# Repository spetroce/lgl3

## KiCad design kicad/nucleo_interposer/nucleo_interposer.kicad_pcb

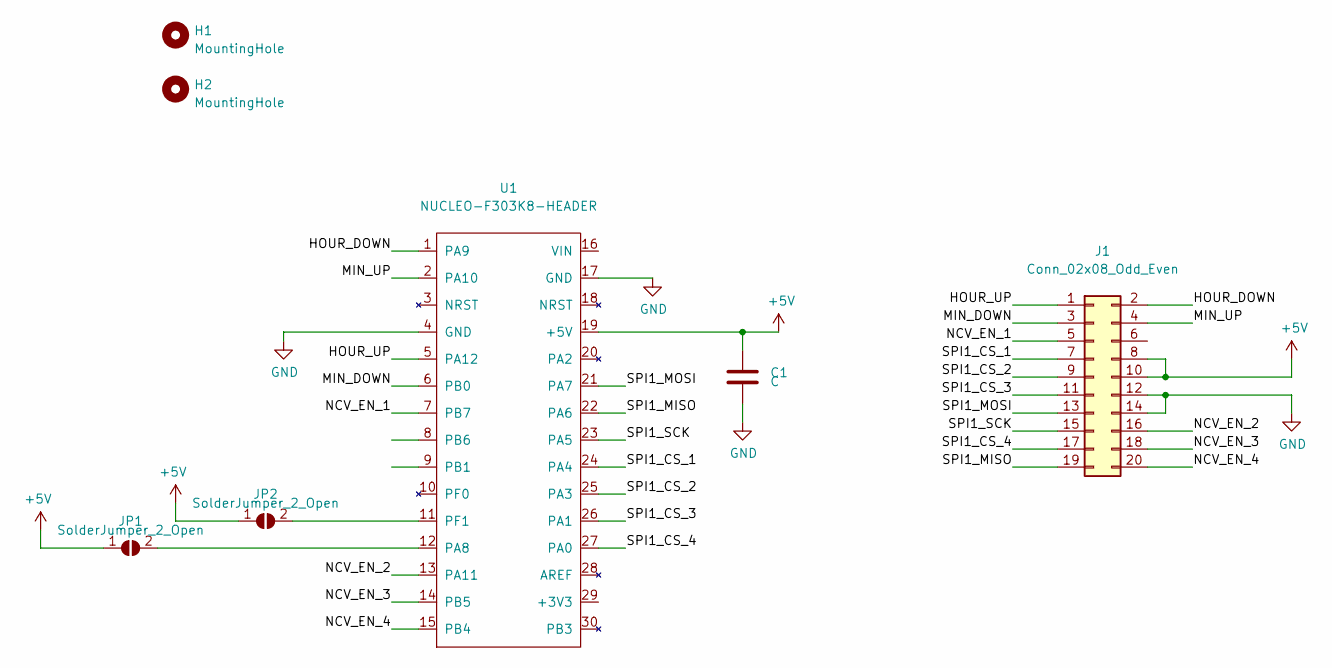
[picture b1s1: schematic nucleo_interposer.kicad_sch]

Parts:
C1: C; C_1206_3216Metric
H1, H2: MountingHole; MountingHole_3.2mm_M3
J1: Conn_02x08_Odd_Even; PinHeader_2x10_P2.54mm_Vertical
JP1, JP2: SolderJumper_2_Open; SolderJumper-2_P1.3mm_Open_TrianglePad1.0x1.5mm
U1: NUCLEO-F303K8-HEADER

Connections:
+5V: C1.2, J1.8, J1.10, JP1.1 (A), JP2.1 (A), U1.19 (+5V)
/HOUR_DOWN: J1.2, U1.1 (PA9)
/HOUR_UP: J1.1, U1.5 (PA12)
/MIN_DOWN: J1.3, U1.6 (PB0)
/MIN_UP: J1.4, U1.2 (PA10)
/NCV_EN_1: J1.5, U1.7 (PB7)
/NCV_EN_2: J1.16, U1.13 (PA11)
/NCV_EN_3: J1.18, U1.14 (PB5)
/NCV_EN_4: J1.20, U1.15 (PB4)
/SPI1_CS_1: J1.7, U1.24 (PA4)
/SPI1_CS_2: J1.9, U1.25 (PA3)
/SPI1_CS_3: J1.11, U1.26 (PA1)
/SPI1_CS_4: J1.17, U1.27 (PA0)
/SPI1_MISO: J1.19, U1.22 (PA6)
/SPI1_MOSI: J1.13, U1.21 (PA7)
/SPI1_SCK: J1.15, U1.23 (PA5)
GND: C1.1, J1.12, J1.14, U1.4 (GND), U1.17 (GND)
unnamed: JP1.2 (B), U1.12 (PA8)
unnamed: JP2.2 (B), U1.11 (PF1)

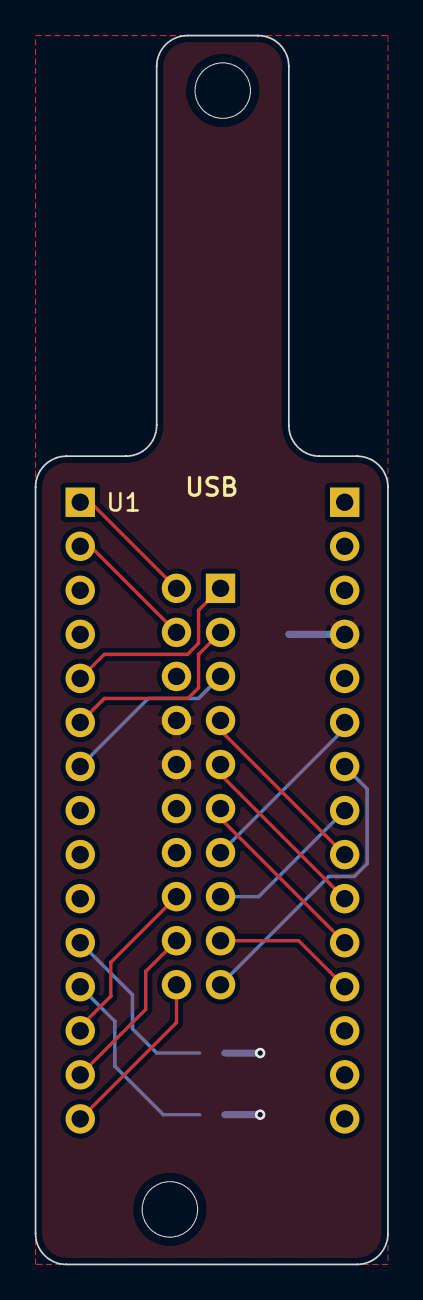
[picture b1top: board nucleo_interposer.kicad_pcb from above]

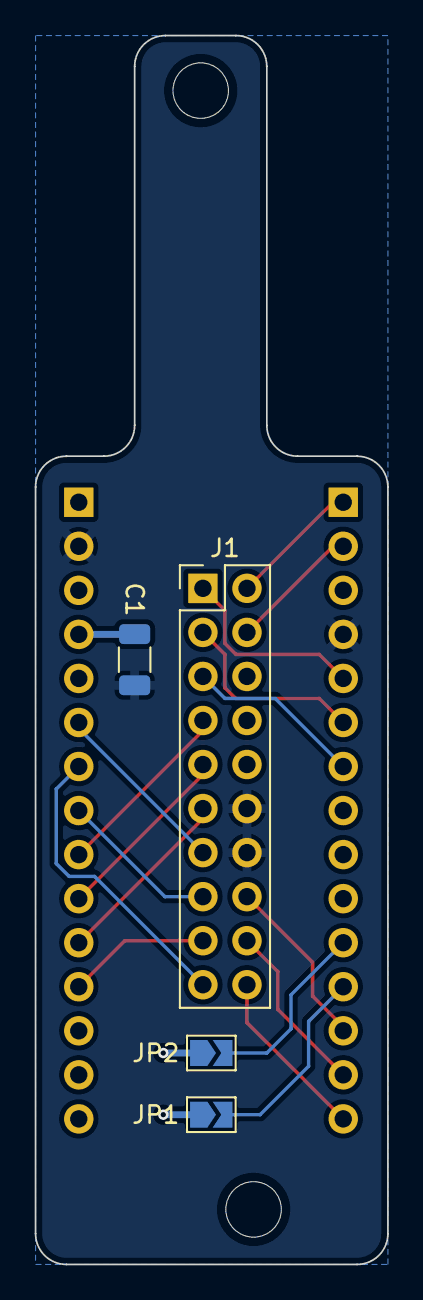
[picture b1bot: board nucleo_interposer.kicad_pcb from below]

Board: 2 copper layers, 20.3 x 70.9 mm, 7 parts (4 on the bottom side), 19 nets.

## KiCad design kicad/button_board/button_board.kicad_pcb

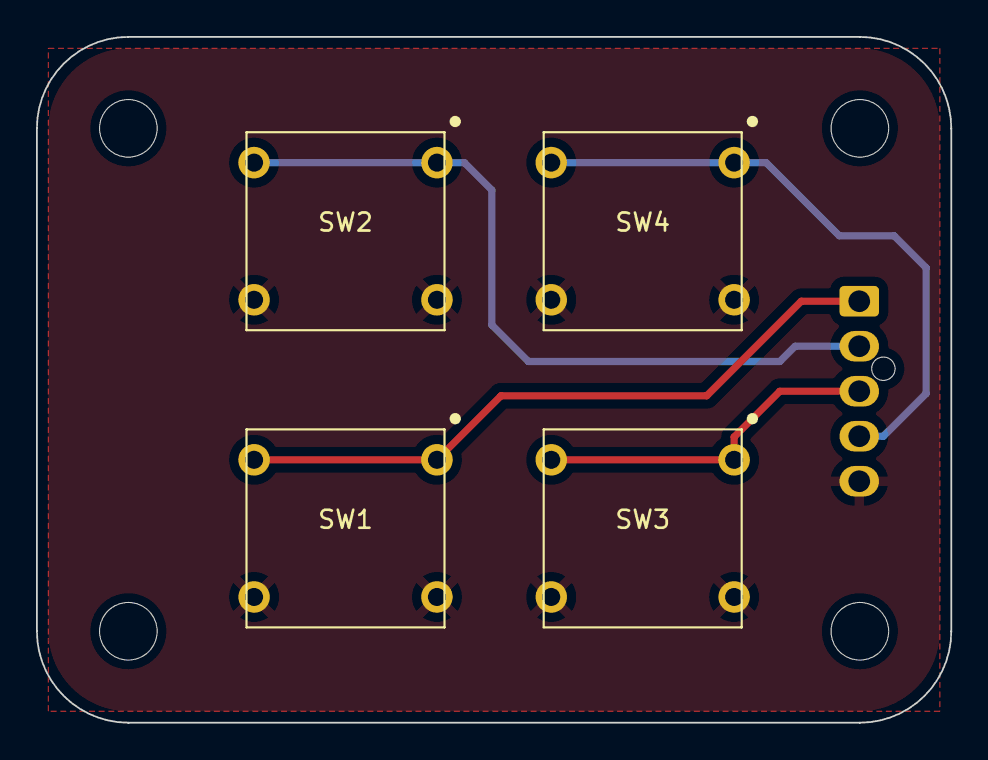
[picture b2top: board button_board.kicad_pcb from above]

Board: 2 copper layers, 50.8 x 38.1 mm, 9 parts (1 on the bottom side), 5 nets.

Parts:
H1, H2, H3, H4: MountingHole; MountingHole_3.2mm_M3
J1: Conn_01x05_Male; Molex_Nano-Fit_105309-xx05_1x05_P2.50mm_Vertical
SW1, SW2, SW3, SW4: apem-3eth9-15.0; 3ETH9-15.0

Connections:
/HOUR_DOWN: J1.1, SW1.1, SW1.2
/HOUR_UP: J1.2, SW2.1, SW2.2
/MIN_DOWN: J1.3, SW3.1, SW3.2
/MIN_UP: J1.4, SW4.1, SW4.2
GND: J1.5, SW1.3, SW1.4, SW2.3, SW2.4, SW3.3, SW3.4, SW4.3, SW4.4

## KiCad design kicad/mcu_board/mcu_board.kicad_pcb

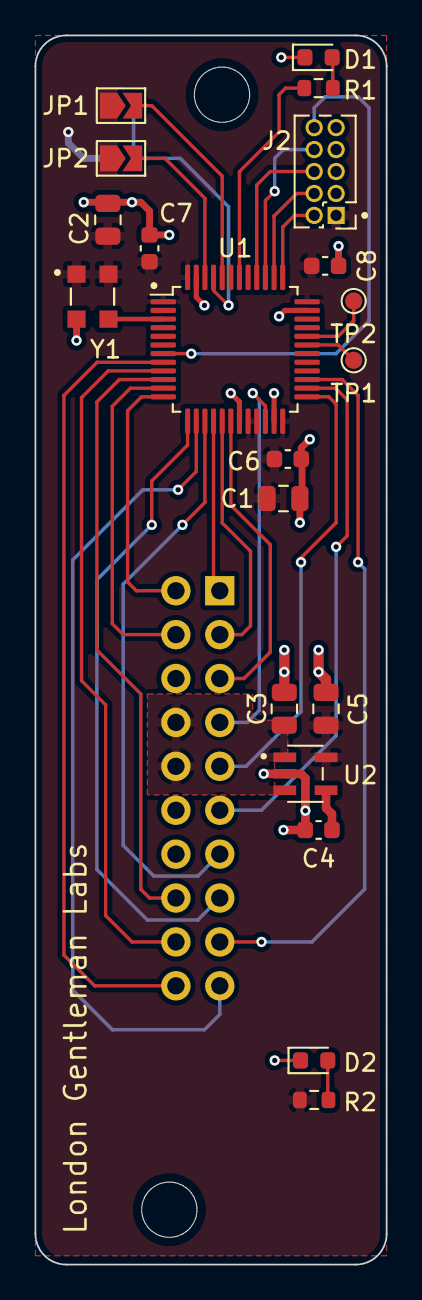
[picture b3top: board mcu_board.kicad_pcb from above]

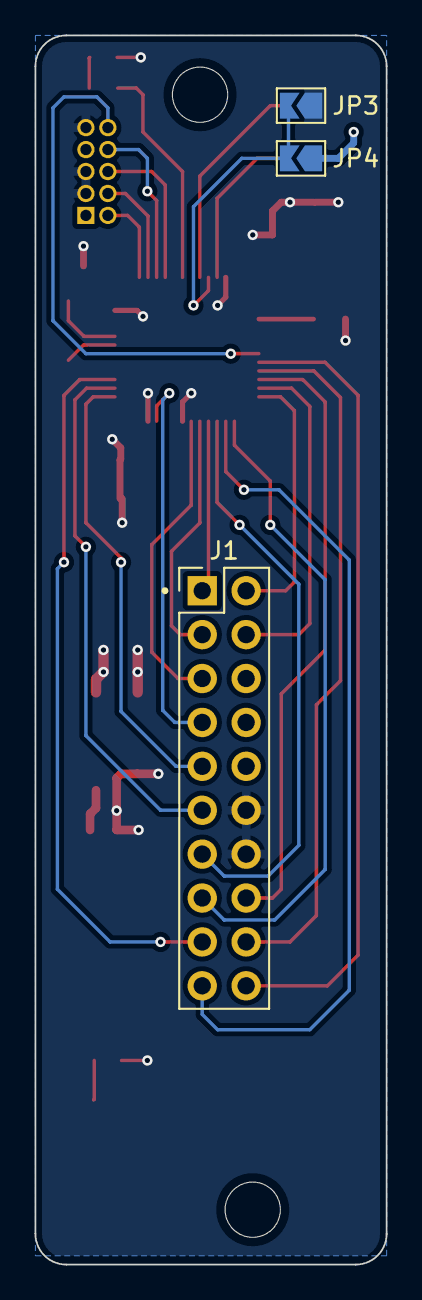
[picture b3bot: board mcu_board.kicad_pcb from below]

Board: 2 copper layers, 20.3 x 71.1 mm, 25 parts (3 on the bottom side), 33 nets.

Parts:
C1, C5: 10uF; C_0805_2012Metric
C2, C3: 1uF; C_0805_2012Metric
C4: 10nF; C_0603_1608Metric
C6, C7, C8: 100nF; C_0603_1608Metric
D1, D2: LED; LED_0603_1608Metric
H1, H2: MountingHole; MountingHole_3.2mm_M3
J1: Conn_02x08_Odd_Even; PinHeader_2x10_P2.54mm_Vertical
J2: Conn_02x05_Odd_Even; PinHeader_2x05_P1.27mm_Vertical
JP1, JP2, JP3, JP4: SolderJumper_2_Open; SolderJumper-2_P1.3mm_Open_TrianglePad1.0x1.5mm
R1, R2: 200; R_0603_1608Metric
TP1, TP2: TestPoint; TestPoint_Pad_D1.0mm
U1: STM32G431CBTx; LQFP-48_7x7mm_P0.5mm
U2: LD2985BM33R; SOT23-5L_STM
Y1: ECS-327TXO-33-TR

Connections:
+3V3: C1.1, C2.2, C5.2, C6.1, C7.2, C8.1, J2.1, JP1.1 (A), JP2.1 (A), JP4.1 (A), R2.1, U1.1 (VBAT), U1.20 (VREF+), U1.21 (VDDA), U1.24 (VDD), U1.36 (VDD), U1.48 (VDD), U2.5 (OUT), Y1.1 (OE), Y1.4 (SUPPLY_VOLTAGE)
+5V: C3.2, J1.8, J1.10, U2.1 (IN), U2.3 (INHIBIT)
/BOOT0: JP3.2 (B), JP4.2 (B), U1.45 (PB8-BOOT0)
/HOUR_DOWN: J1.2, U1.12 (PA4)
/HOUR_UP: J1.1, U1.16 (PB0)
/HW_REV_1: JP1.2 (B), U1.44 (PB7)
/HW_REV_2: JP2.2 (B), U1.46 (PB9)
/LED_GREEN: R1.1, U1.42 (PB5)
/MIN_DOWN: J1.3, U1.17 (PB1)
/MIN_UP: J1.4, U1.11 (PA3)
/NCV_EN_1: J1.5, U1.18 (PB2)
/NCV_EN_2: J1.16, U1.10 (PA2)
/NCV_EN_3: J1.18, U1.9 (PA1)
/NCV_EN_4: J1.20, U1.8 (PA0)
/NRST: J2.10, U1.7 (PG10-NRST)
/RCC_OSC32_IN: U1.3 (PC14-OSC32_IN), Y1.3 (OUTPUT)
/SPI1_CS_1: J1.7, U1.22 (PB10)
/SPI1_CS_2: J1.9, U1.25 (PB11)
/SPI1_CS_3: J1.11, U1.26 (PB12)
/SPI1_CS_4: J1.17, U1.27 (PB13)
/SPI1_MISO: J1.19, U1.14 (PA6)
/SPI1_MOSI: J1.13, U1.15 (PA7)
/SPI1_SCK: J1.15, U1.13 (PA5)
/SYS_JTCK-SWCLK: J2.4, U1.38 (PA14)
/SYS_JTDI: J2.8, U1.39 (PA15)
/SYS_JTDO-SWO: J2.6, U1.40 (PB3)
/SYS_JTMS-SWDIO: J2.2, U1.37 (PA13)
GND: C1.2, C2.1, C3.1, C4.1, C5.1, C6.2, C7.1, C8.2, D1.1 (K), D2.1 (K), J1.12, J1.14, J2.3, J2.5, J2.9, JP3.1 (A), U1.19 (VSSA), U1.23 (VSS), U1.35 (VSS), U1.47 (VSS), U2.2 (GND), Y1.2 (GND)
unnamed: D1.2 (A), R1.2
unnamed: D2.2 (A), R2.2
unnamed: TP1.1, U1.31 (PA9)
unnamed: TP2.1, U1.32 (PA10)
unnamed: C4.2, U2.4 (BYPASS)

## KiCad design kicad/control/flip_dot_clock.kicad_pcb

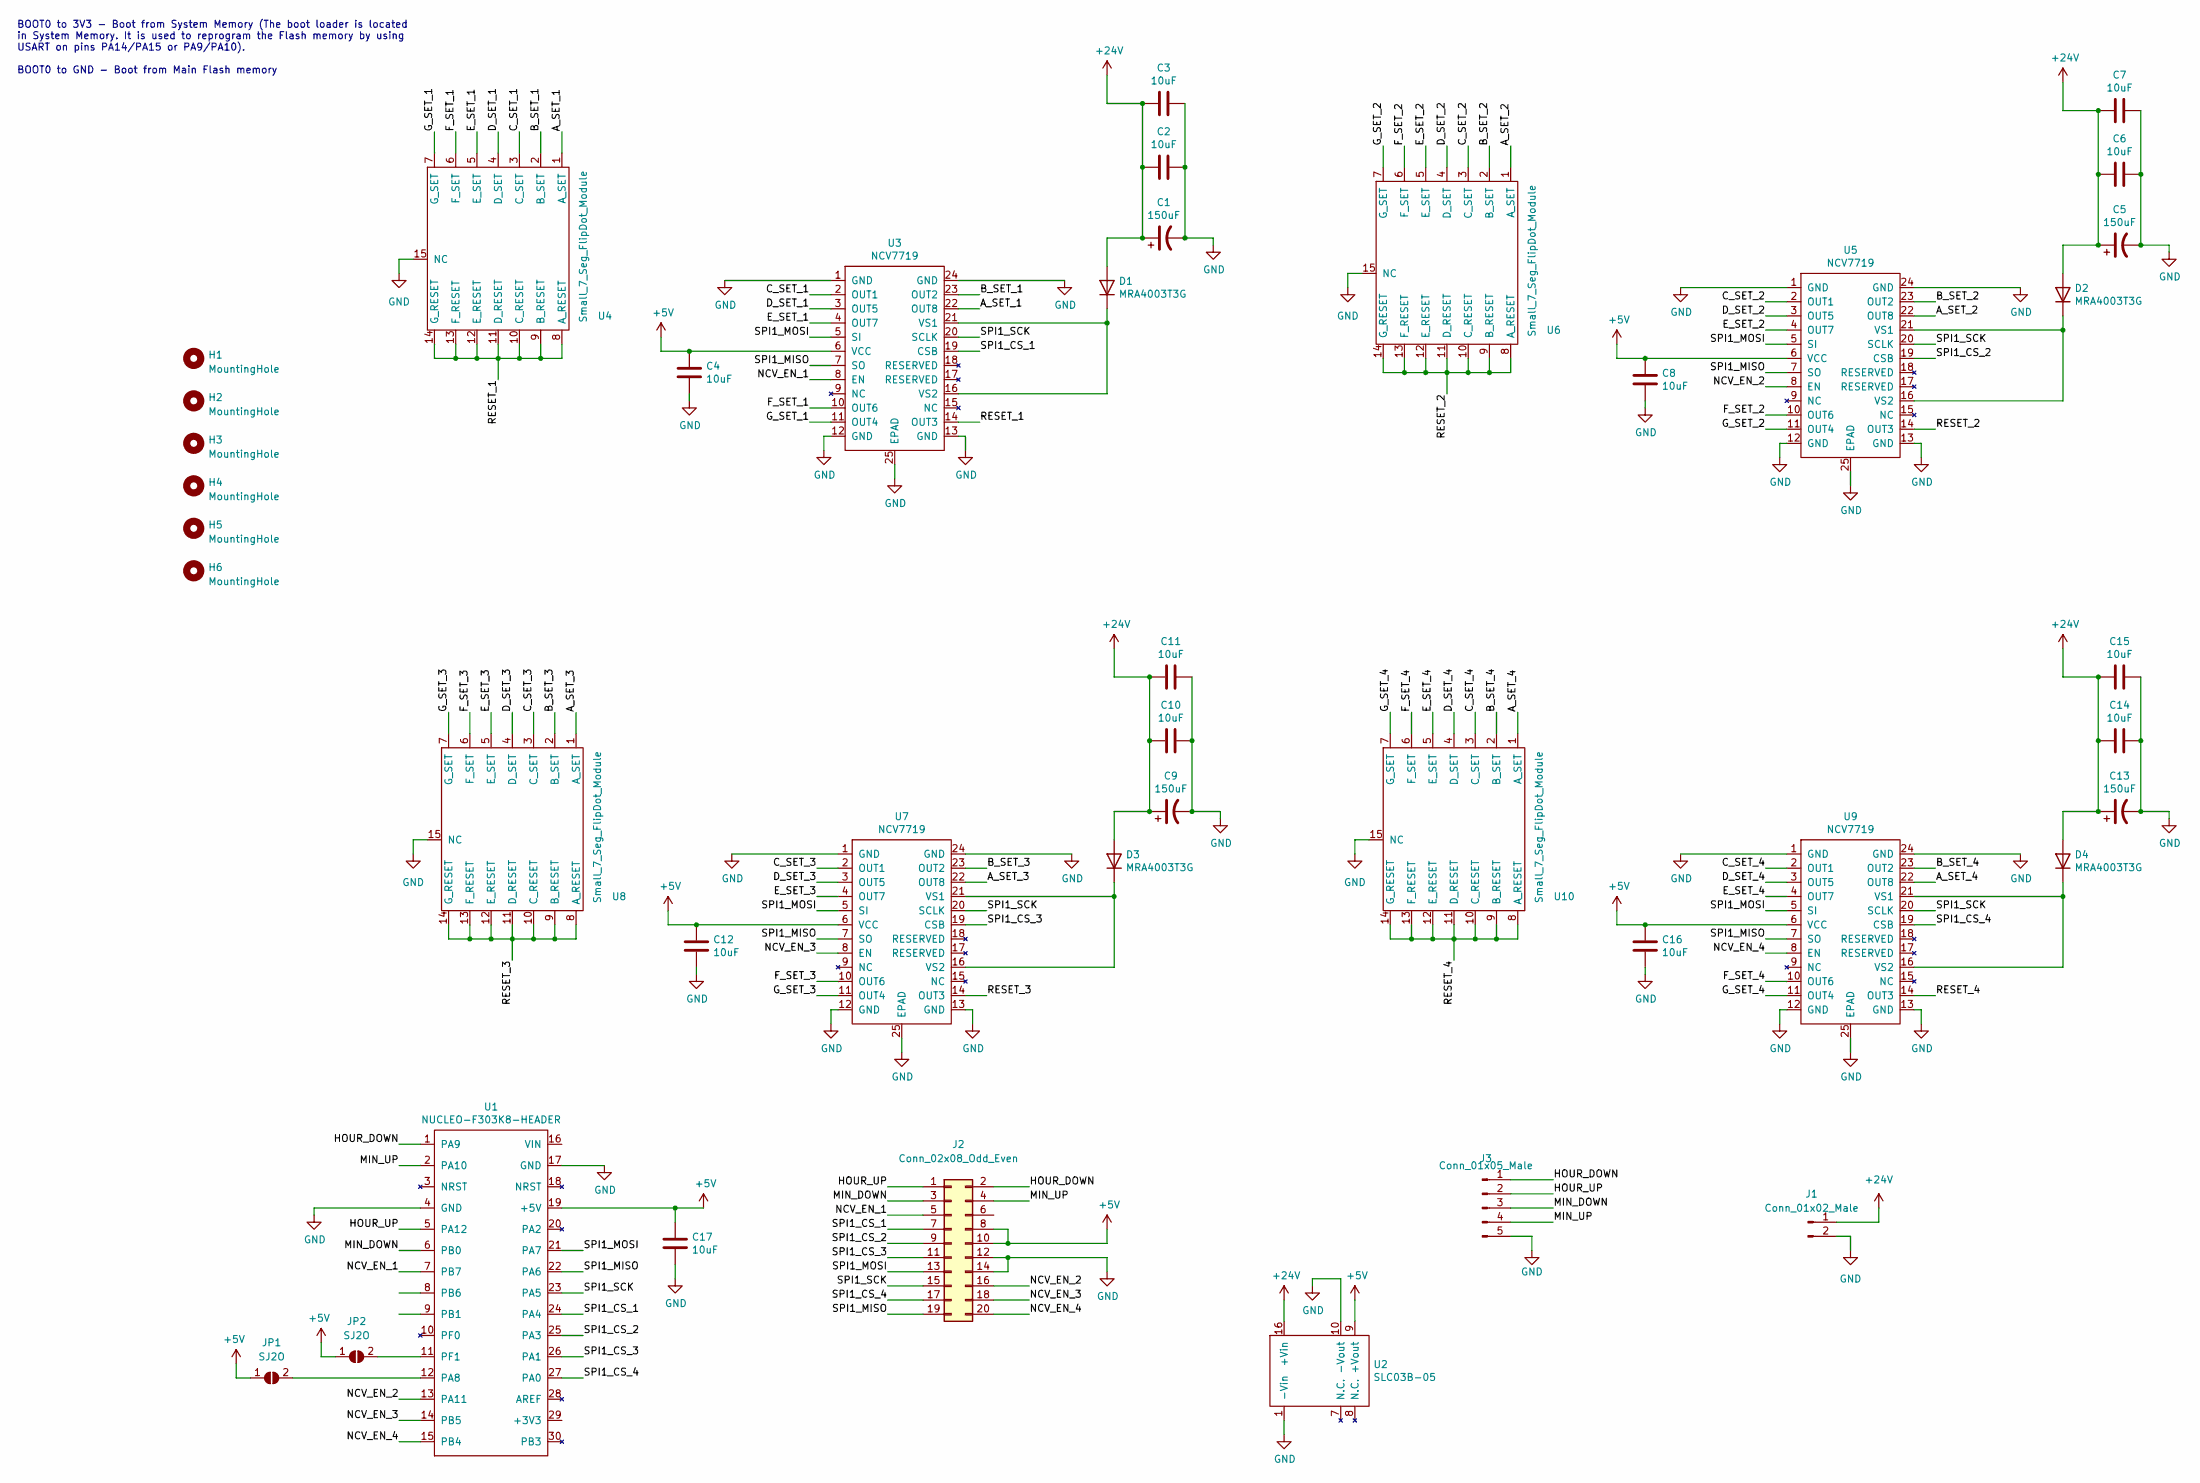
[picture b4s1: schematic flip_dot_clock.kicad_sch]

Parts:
C1, C5, C9, C13: 150uF; CP_Radial_D10.0mm_P5.00mm
C2, C3, C4, C6, C7, C8, C10, C11, C12, C14, C15, C16, C17: 10uF; C_1206_3216Metric
D1, D2, D3, D4: MRA4003T3G; D_SMA
H1, H2, H3, H4, H5, H6: MountingHole; MountingHole_3.2mm_M3
J1: Conn_01x02_Male; Molex_Micro-Fit_3.0_43650-0215_1x02_P3.00mm_Vertical
J2: Conn_02x08_Odd_Even; PinSocket_2x10_P2.54mm_Vertical
J3: Conn_01x05_Male; Molex_Nano-Fit_105309-xx05_1x05_P2.50mm_Vertical
JP1, JP2: SJ2O; SolderJumper-2_P1.3mm_Open_TrianglePad1.0x1.5mm
U1: NUCLEO-F303K8-HEADER
U2: SLC03B-05
U3, U5, U7, U9: NCV7719; SSOP-24_6.4x7.55mm_P0.65mm
U4, U6, U8, U10: Small_7_Seg_FlipDot_Module

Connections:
+5V: C4.1, C8.1, C12.1, C16.1, C17.1, J2.8, J2.10, JP1.1 (A), JP2.1 (A), U1.19 (+5V), U2.9 (+Vout), U3.6 (VCC), U5.6 (VCC), U7.6 (VCC), U9.6 (VCC)
+24V: C1.1, C2.2, C3.2, C5.1, C6.2, C7.2, C9.1, C10.2, C11.2, C13.1, C14.2, C15.2, D1.2 (A), D2.2 (A), D3.2 (A), D4.2 (A), J1.1, U2.16 (+Vin)
/A_SET_1: U3.22 (OUT8), U4.1 (A_SET)
/A_SET_2: U5.22 (OUT8), U6.1 (A_SET)
/A_SET_3: U7.22 (OUT8), U8.1 (A_SET)
/A_SET_4: U9.22 (OUT8), U10.1 (A_SET)
/B_SET_1: U3.23 (OUT2), U4.2 (B_SET)
/B_SET_2: U5.23 (OUT2), U6.2 (B_SET)
/B_SET_3: U7.23 (OUT2), U8.2 (B_SET)
/B_SET_4: U9.23 (OUT2), U10.2 (B_SET)
/C_SET_1: U3.2 (OUT1), U4.3 (C_SET)
/C_SET_2: U5.2 (OUT1), U6.3 (C_SET)
/C_SET_3: U7.2 (OUT1), U8.3 (C_SET)
/C_SET_4: U9.2 (OUT1), U10.3 (C_SET)
/D_SET_1: U3.3 (OUT5), U4.4 (D_SET)
/D_SET_2: U5.3 (OUT5), U6.4 (D_SET)
/D_SET_3: U7.3 (OUT5), U8.4 (D_SET)
/D_SET_4: U9.3 (OUT5), U10.4 (D_SET)
/E_SET_1: U3.4 (OUT7), U4.5 (E_SET)
/E_SET_2: U5.4 (OUT7), U6.5 (E_SET)
/E_SET_3: U7.4 (OUT7), U8.5 (E_SET)
/E_SET_4: U9.4 (OUT7), U10.5 (E_SET)
/F_SET_1: U3.10 (OUT6), U4.6 (F_SET)
/F_SET_2: U5.10 (OUT6), U6.6 (F_SET)
/F_SET_3: U7.10 (OUT6), U8.6 (F_SET)
/F_SET_4: U9.10 (OUT6), U10.6 (F_SET)
/G_SET_1: U3.11 (OUT4), U4.7 (G_SET)
/G_SET_2: U5.11 (OUT4), U6.7 (G_SET)
/G_SET_3: U7.11 (OUT4), U8.7 (G_SET)
/G_SET_4: U9.11 (OUT4), U10.7 (G_SET)
/HOUR_DOWN: J2.2, J3.1, U1.1 (PA9)
/HOUR_UP: J2.1, J3.2, U1.5 (PA12)
/MIN_DOWN: J2.3, J3.3, U1.6 (PB0)
/MIN_UP: J2.4, J3.4, U1.2 (PA10)
/NCV_EN_1: J2.5, U1.7 (PB7), U3.8 (EN)
/NCV_EN_2: J2.16, U1.13 (PA11), U5.8 (EN)
/NCV_EN_3: J2.18, U1.14 (PB5), U7.8 (EN)
/NCV_EN_4: J2.20, U1.15 (PB4), U9.8 (EN)
/RESET_1: U3.14 (OUT3), U4.8 (A_RESET), U4.9 (B_RESET), U4.10 (C_RESET), U4.11 (D_RESET), U4.12 (E_RESET), U4.13 (F_RESET), U4.14 (G_RESET)
/RESET_2: U5.14 (OUT3), U6.8 (A_RESET), U6.9 (B_RESET), U6.10 (C_RESET), U6.11 (D_RESET), U6.12 (E_RESET), U6.13 (F_RESET), U6.14 (G_RESET)
/RESET_3: U7.14 (OUT3), U8.8 (A_RESET), U8.9 (B_RESET), U8.10 (C_RESET), U8.11 (D_RESET), U8.12 (E_RESET), U8.13 (F_RESET), U8.14 (G_RESET)
/RESET_4: U9.14 (OUT3), U10.8 (A_RESET), U10.9 (B_RESET), U10.10 (C_RESET), U10.11 (D_RESET), U10.12 (E_RESET), U10.13 (F_RESET), U10.14 (G_RESET)
/SPI1_CS_1: J2.7, U1.24 (PA4), U3.19 (CSB)
/SPI1_CS_2: J2.9, U1.25 (PA3), U5.19 (CSB)
/SPI1_CS_3: J2.11, U1.26 (PA1), U7.19 (CSB)
/SPI1_CS_4: J2.17, U1.27 (PA0), U9.19 (CSB)
/SPI1_MISO: J2.19, U1.22 (PA6), U3.7 (SO), U5.7 (SO), U7.7 (SO), U9.7 (SO)
/SPI1_MOSI: J2.13, U1.21 (PA7), U3.5 (SI), U5.5 (SI), U7.5 (SI), U9.5 (SI)
/SPI1_SCK: J2.15, U1.23 (PA5), U3.20 (SCLK), U5.20 (SCLK), U7.20 (SCLK), U9.20 (SCLK)
GND: C1.2, C2.1, C3.1, C4.2, C5.2, C6.1, C7.1, C8.2, C9.2, C10.1, C11.1, C12.2, C13.2, C14.1, C15.1, C16.2, C17.2, J1.2, J2.12, J2.14, J3.5, U1.4 (GND), U1.17 (GND), U2.1 (-Vin), U2.10 (-Vout), U3.1 (GND), U3.12 (GND), U3.13 (GND), U3.24 (GND), U3.25 (EPAD), U4.15 (NC), U5.1 (GND), U5.12 (GND), U5.13 (GND), U5.24 (GND), U5.25 (EPAD), U6.15 (NC), U7.1 (GND), U7.12 (GND), U7.13 (GND), U7.24 (GND), U7.25 (EPAD), U8.15 (NC), U9.1 (GND), U9.12 (GND), U9.13 (GND), U9.24 (GND), U9.25 (EPAD), U10.15 (NC)
unnamed: D1.1 (K), U3.16 (VS2), U3.21 (VS1)
unnamed: D2.1 (K), U5.16 (VS2), U5.21 (VS1)
unnamed: D3.1 (K), U7.16 (VS2), U7.21 (VS1)
unnamed: D4.1 (K), U9.16 (VS2), U9.21 (VS1)
unnamed: JP1.2 (B), U1.12 (PA8)
unnamed: JP2.2 (B), U1.11 (PF1)

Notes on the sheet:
BOOT0 to 3V3 - Boot from System Memory (The boot loader is located in System Memory. It is used to reprogram the Flash memory by using USART on pins PA14/PA15 or PA9/PA10). BOOT0 to GND - Boot from Main Flash memory

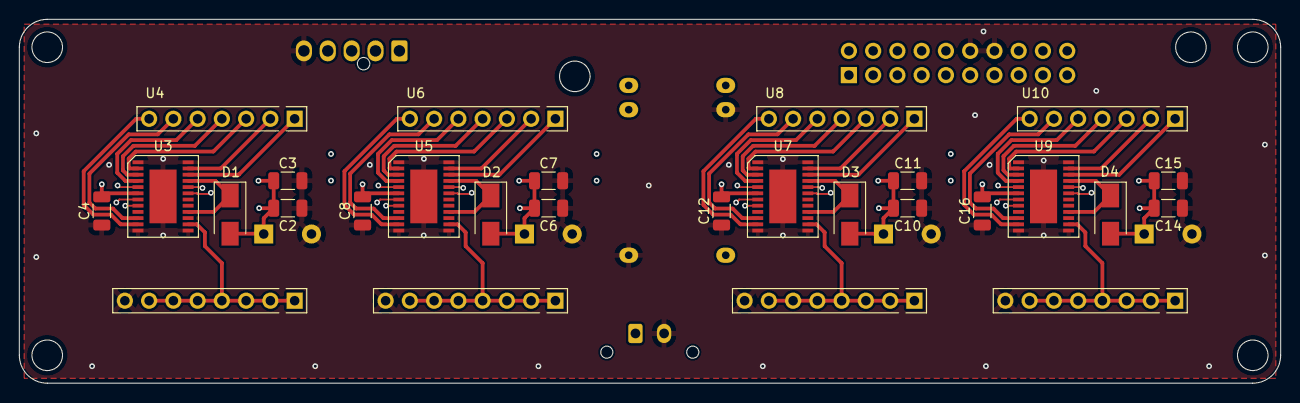
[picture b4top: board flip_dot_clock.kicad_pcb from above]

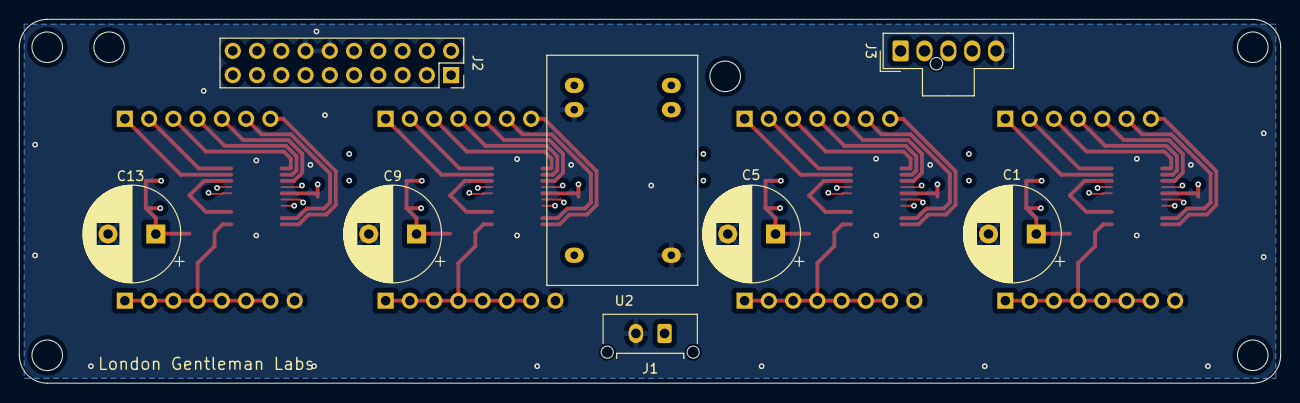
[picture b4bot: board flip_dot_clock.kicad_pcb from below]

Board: 4 copper layers, 132.1 x 38.1 mm, 38 parts (10 on the bottom side), 54 nets.

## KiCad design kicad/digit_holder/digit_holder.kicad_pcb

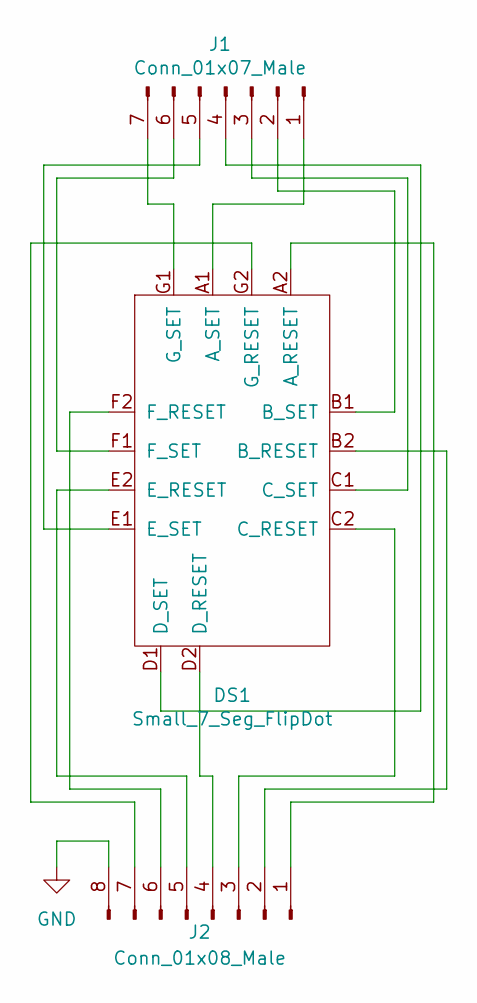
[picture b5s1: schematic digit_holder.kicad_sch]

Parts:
DS1: Small_7_Seg_FlipDot
J1: Conn_01x07_Male; PinHeader_1x07_P2.54mm_Vertical
J2: Conn_01x08_Male; PinHeader_1x08_P2.54mm_Vertical

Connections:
GND: J2.8
unnamed: DS1.A2 (A_RESET), J2.1
unnamed: DS1.A1 (A_SET), J1.1
unnamed: DS1.B2 (B_RESET), J2.2
unnamed: DS1.B1 (B_SET), J1.2
unnamed: DS1.C2 (C_RESET), J2.3
unnamed: DS1.C1 (C_SET), J1.3
unnamed: DS1.D2 (D_RESET), J2.4
unnamed: DS1.D1 (D_SET), J1.4
unnamed: DS1.E2 (E_RESET), J2.5
unnamed: DS1.E1 (E_SET), J1.5
unnamed: DS1.F2 (F_RESET), J2.6
unnamed: DS1.F1 (F_SET), J1.6
unnamed: DS1.G2 (G_RESET), J2.7
unnamed: DS1.G1 (G_SET), J1.7

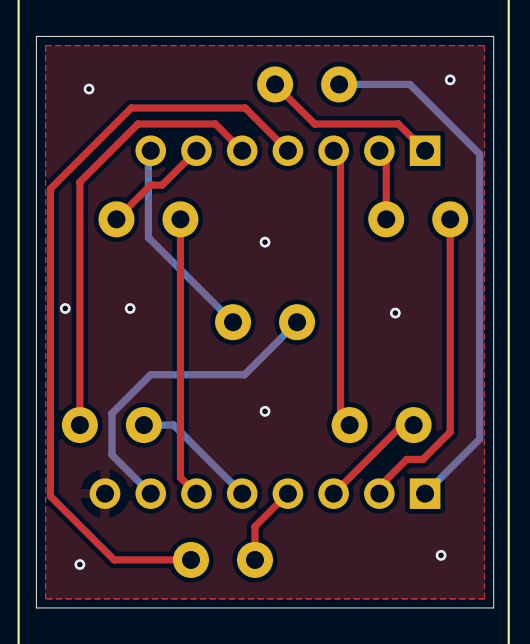
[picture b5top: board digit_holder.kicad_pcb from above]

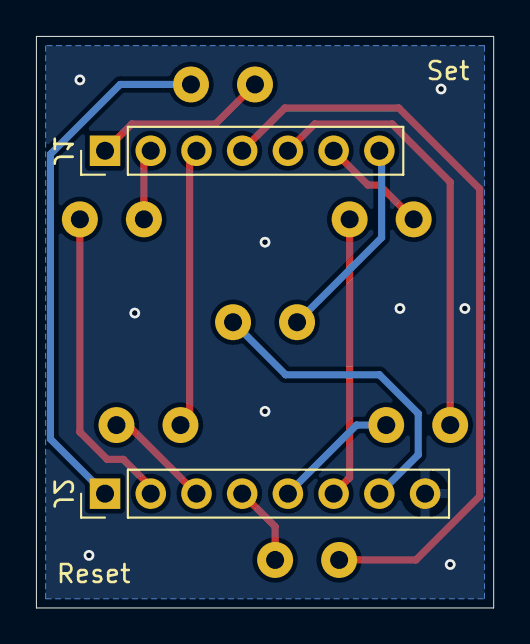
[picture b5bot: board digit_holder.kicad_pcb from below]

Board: 2 copper layers, 25.4 x 31.8 mm, 3 parts (2 on the bottom side), 14 nets.

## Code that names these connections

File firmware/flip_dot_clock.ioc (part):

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Mcu.Name=STM32G431C(6-8-B)Tx
Mcu.Package=LQFP48
Mcu.UserName=STM32G431CBTx
PA0.GPIOParameters=GPIO_Speed,GPIO_Label
PA0.GPIO_Label=NCV_EN_4
PA0.GPIO_Speed=GPIO_SPEED_FREQ_VERY_HIGH
PA0.Signal=GPIO_Output
PA1.GPIOParameters=GPIO_Speed,GPIO_Label
PA1.GPIO_Label=NCV_EN_3
PA1.GPIO_Speed=GPIO_SPEED_FREQ_VERY_HIGH
PA1.Signal=GPIO_Output
PA10.Signal=USART1_RX
PA13.Mode=JTAG_5_pins
PA13.Signal=SYS_JTMS-SWDIO
PA14.Mode=JTAG_5_pins
PA14.Signal=SYS_JTCK-SWCLK
PA15.Mode=JTAG_5_pins
PA15.Signal=SYS_JTDI
PA2.GPIOParameters=GPIO_Speed,GPIO_Label
PA2.GPIO_Label=NCV_EN_2
PA2.GPIO_Speed=GPIO_SPEED_FREQ_VERY_HIGH
PA2.Signal=GPIO_Output
PA3.GPIOParameters=GPIO_PuPd,GPIO_Label
PA3.GPIO_Label=HOUR_DOWN
PA3.GPIO_PuPd=GPIO_PULLUP
PA3.Signal=GPIO_Input
PA4.GPIOParameters=GPIO_PuPd,GPIO_Label
PA4.GPIO_Label=MIN_UP
PA4.GPIO_PuPd=GPIO_PULLUP
PA4.Signal=GPIO_Input
PA5.Mode=Full_Duplex_Master
PA5.Signal=SPI1_SCK
PA6.Mode=Full_Duplex_Master
PA6.Signal=SPI1_MISO
PA7.Mode=Full_Duplex_Master
PA7.Signal=SPI1_MOSI
PA9.Signal=USART1_TX
PB0.GPIOParameters=GPIO_PuPd,GPIO_Label
PB0.GPIO_Label=HOUR_UP
PB0.GPIO_PuPd=GPIO_PULLUP
PB0.Signal=GPIO_Input
PB1.GPIOParameters=GPIO_PuPd,GPIO_Label
PB1.GPIO_Label=MIN_DOWN
PB1.GPIO_PuPd=GPIO_PULLUP
PB1.Signal=GPIO_Input
PB10.GPIOParameters=GPIO_Speed,GPIO_Label
PB10.GPIO_Label=SPI1_CS_1
PB10.GPIO_Speed=GPIO_SPEED_FREQ_VERY_HIGH
PB10.Signal=GPIO_Output
PB11.GPIOParameters=GPIO_Speed,GPIO_Label
PB11.GPIO_Label=SPI1_CS_2
PB11.GPIO_Speed=GPIO_SPEED_FREQ_VERY_HIGH
PB11.Signal=GPIO_Output
PB12.GPIOParameters=GPIO_Speed,GPIO_Label
PB12.GPIO_Label=SPI1_CS_3
PB12.GPIO_Speed=GPIO_SPEED_FREQ_VERY_HIGH
PB12.Signal=GPIO_Output
PB13.GPIOParameters=GPIO_Speed,GPIO_Label
PB13.GPIO_Label=SPI1_CS_4
PB13.GPIO_Speed=GPIO_SPEED_FREQ_VERY_HIGH
PB13.Signal=GPIO_Output
PB2.GPIOParameters=GPIO_Speed,GPIO_Label
PB2.GPIO_Label=NCV_EN_1
PB2.GPIO_Speed=GPIO_SPEED_FREQ_VERY_HIGH
PB2.Signal=GPIO_Output
PB3.Mode=JTAG_5_pins
PB3.Signal=SYS_JTDO-SWO
PB4.Mode=JTAG_5_pins
PB4.Signal=SYS_JTRST
PB5.GPIOParameters=GPIO_Speed,GPIO_Label
PB5.GPIO_Label=LED_GREEN
PB5.GPIO_Speed=GPIO_SPEED_FREQ_VERY_HIGH
PB5.Signal=GPIO_Output
PB7.GPIOParameters=GPIO_PuPd,GPIO_Label
PB7.GPIO_Label=HW_REV_1
PB7.GPIO_PuPd=GPIO_PULLDOWN
PB7.Signal=GPIO_Input
PB9.GPIOParameters=GPIO_PuPd,GPIO_Label
PB9.GPIO_Label=HW_REV_2
PB9.GPIO_PuPd=GPIO_PULLDOWN
PB9.Signal=GPIO_Input
PC14-OSC32_IN.Mode=LSE-External-Clock-Source
PC14-OSC32_IN.Signal=RCC_OSC32_IN
RCC.HSE_VALUE=8000000
RCC.SYSCLKFreq_VALUE=160000000
RCC.SYSCLKSource=RCC_SYSCLKSOURCE_PLLCLK
board=custom

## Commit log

2019-12-18 lgl3 - flip dot clock
2019-12-18 add datasheets
2020-02-15 add firmware
2020-02-24 update MCU. update kicad project.
2021-05-27 update MCU
2021-05-27 move to kicad folder
2021-05-27 add PDFs
2021-05-27 add SPI
2021-05-27 restart kicad project
2021-06-21 backup
2021-07-11 base set digit definitions/func added
2021-07-12 backup commit to save more initial efforts
2021-07-15 update gitiginore
2021-07-25 interlaced digit setting
2021-08-01 update driver, debug LED, bunch of improvements
2021-08-01 get SPI working and timed correctly
2021-08-01 increase sysclk to 64 MHz
2021-08-02 update SPI settings
2021-08-02 change to 03 compile optimization
2021-08-03 fix silly mistake
2021-08-04 add test
2021-08-04 remove comment
2021-08-05 change SPI to LL library
    Noticed that there was a lot of latency in the HAL transmit
    function. It was taking 35us to send two words, with a 5us delay
    in between them. The acutal transmissions take up 7.75us. So that's
    22.25us of delay or roughly 5.55us before and after a chip select
    line toggle. With the LL drivers, the total transmit time is 17us.
    That makes for rougly 1.1us before and after a chip select line
2021-08-14 it works
2021-08-15 improve api
2021-08-17 added hide and show all
2021-08-18 rewrite
    Turns out the ncv7719 chip can only drive two segments at a time.
    All operations have been updated to switch a maximum of two
    segments now. There is a global tx_data buffer and a parallel
    disp_idx buffer that are used to store command sequences. No more
    state machines for setting digits or for showing/hiding all
    segments.
2021-09-20 seven segment holder pcb
2021-09-23 update pcb
2021-11-08 add parts
2021-11-08 new footprint
2021-11-08 update schem
2021-11-14 update parts. add caps
2021-12-27 update parts
2021-12-29 update stm driver
2021-12-30 pcb updates
2021-12-30 add power planes
2022-01-01 all PCB nets connected
2022-01-01 update footprints, adjust power planes
2022-01-01 update power planes, move C17, update EN pin mux
2022-01-02 DRC updates
2022-01-02 update layout, add power connector
2022-01-09 begin PCB redesign based on overall clock dims
2022-01-09 adjust power planes
2022-01-16 fix all the kicad files
2022-02-02 moving along
2022-02-02 update firmware to match new digit layout
    I let the PCB layout dictate the pinout for the NCV driver chip to have
    a more elegant trace layout. This required updating the bitmasks for
    setting the segments and digits.
2022-02-02 flip schematic part
2022-02-05 kicad update
2022-02-05 add nucleo interposer board
2022-02-05 update tracks
2022-02-05 add nucleo interposer step and make it smaller
2022-02-05 move JPS and cap to back
2022-02-07 add digit holder ground planes
2022-02-07 update git ignore
2022-02-08 add mounts for nucleo interposer
2022-02-18 and more ground plane
2022-02-18 fw cleanup
2022-02-19 fill zone update
2022-02-20 add button board. update control ground plane.
2022-02-20 increase track/clearance size
2022-03-03 update kicad
2022-04-16 button repeat
2022-04-16 clean up
2022-10-03 update mcu to stm32g431cbt6 and add tcxo
2022-10-10 update 3d models
2022-10-11 fix LDO bug. FW updates to support new HW
2022-10-11 use 100nF 0603 for bypass cap
2022-10-11 rework LDO section
2022-10-14 layout update for LDO
2022-10-15 LSCO output on PA2
2022-10-17 update 3d model paths
2022-10-18 update model
2022-10-30 add button_board step
2022-10-30 fix button_board step
2023-01-04 move buttons to match clock assembly update
2023-02-04 update kicad version
